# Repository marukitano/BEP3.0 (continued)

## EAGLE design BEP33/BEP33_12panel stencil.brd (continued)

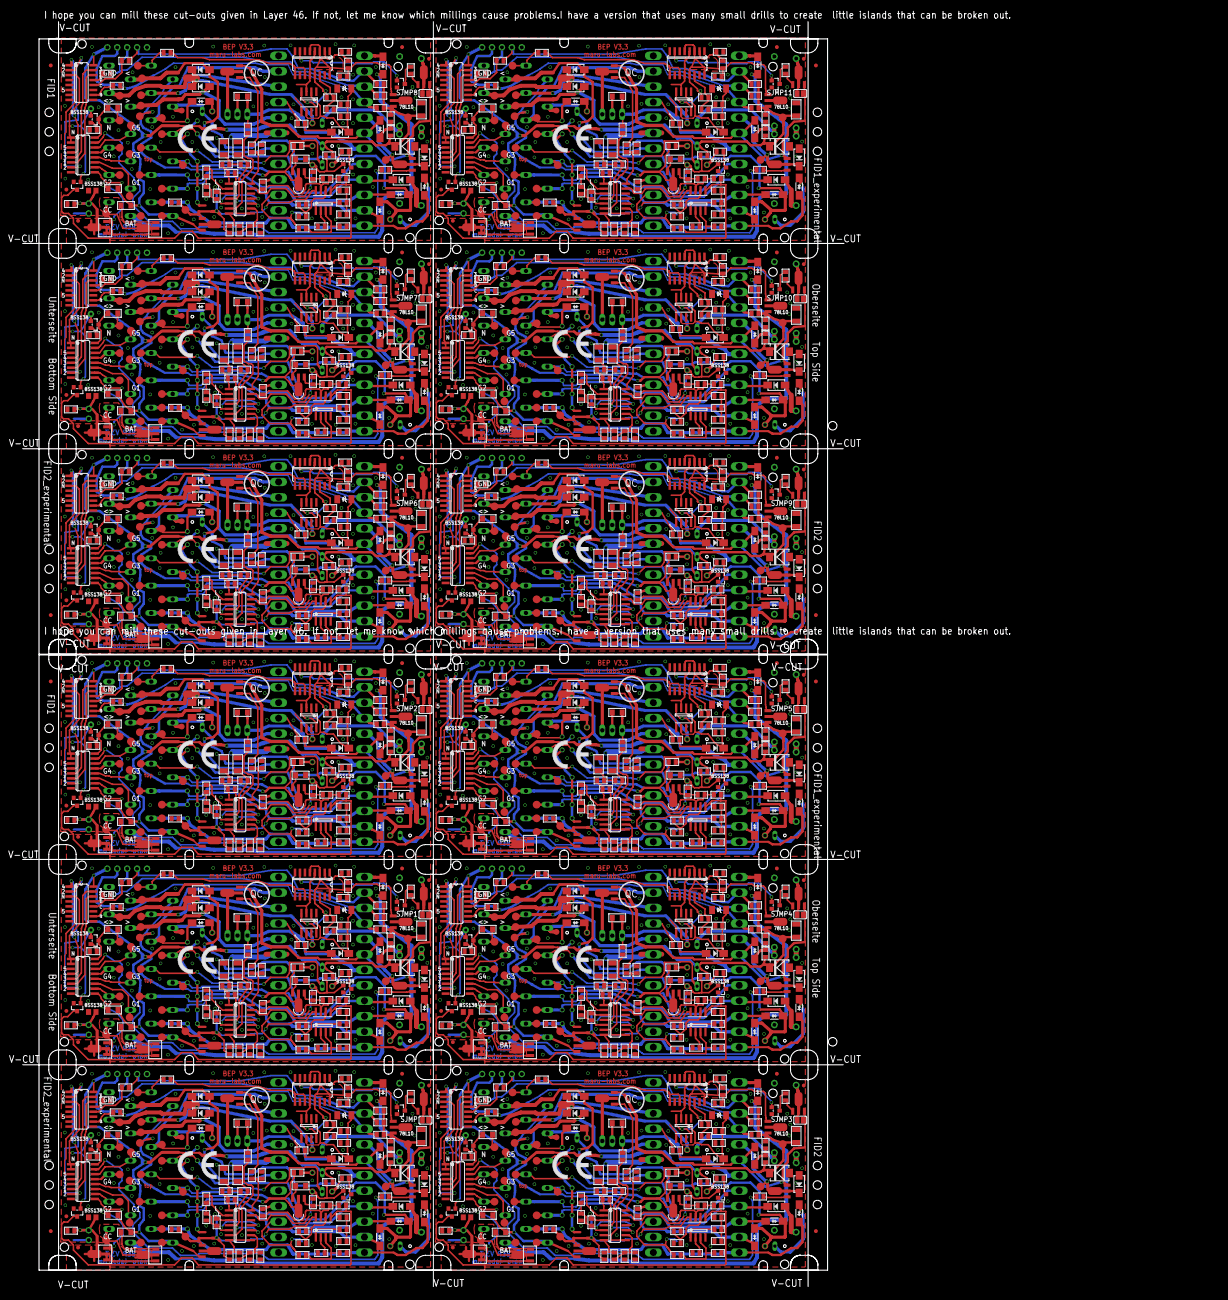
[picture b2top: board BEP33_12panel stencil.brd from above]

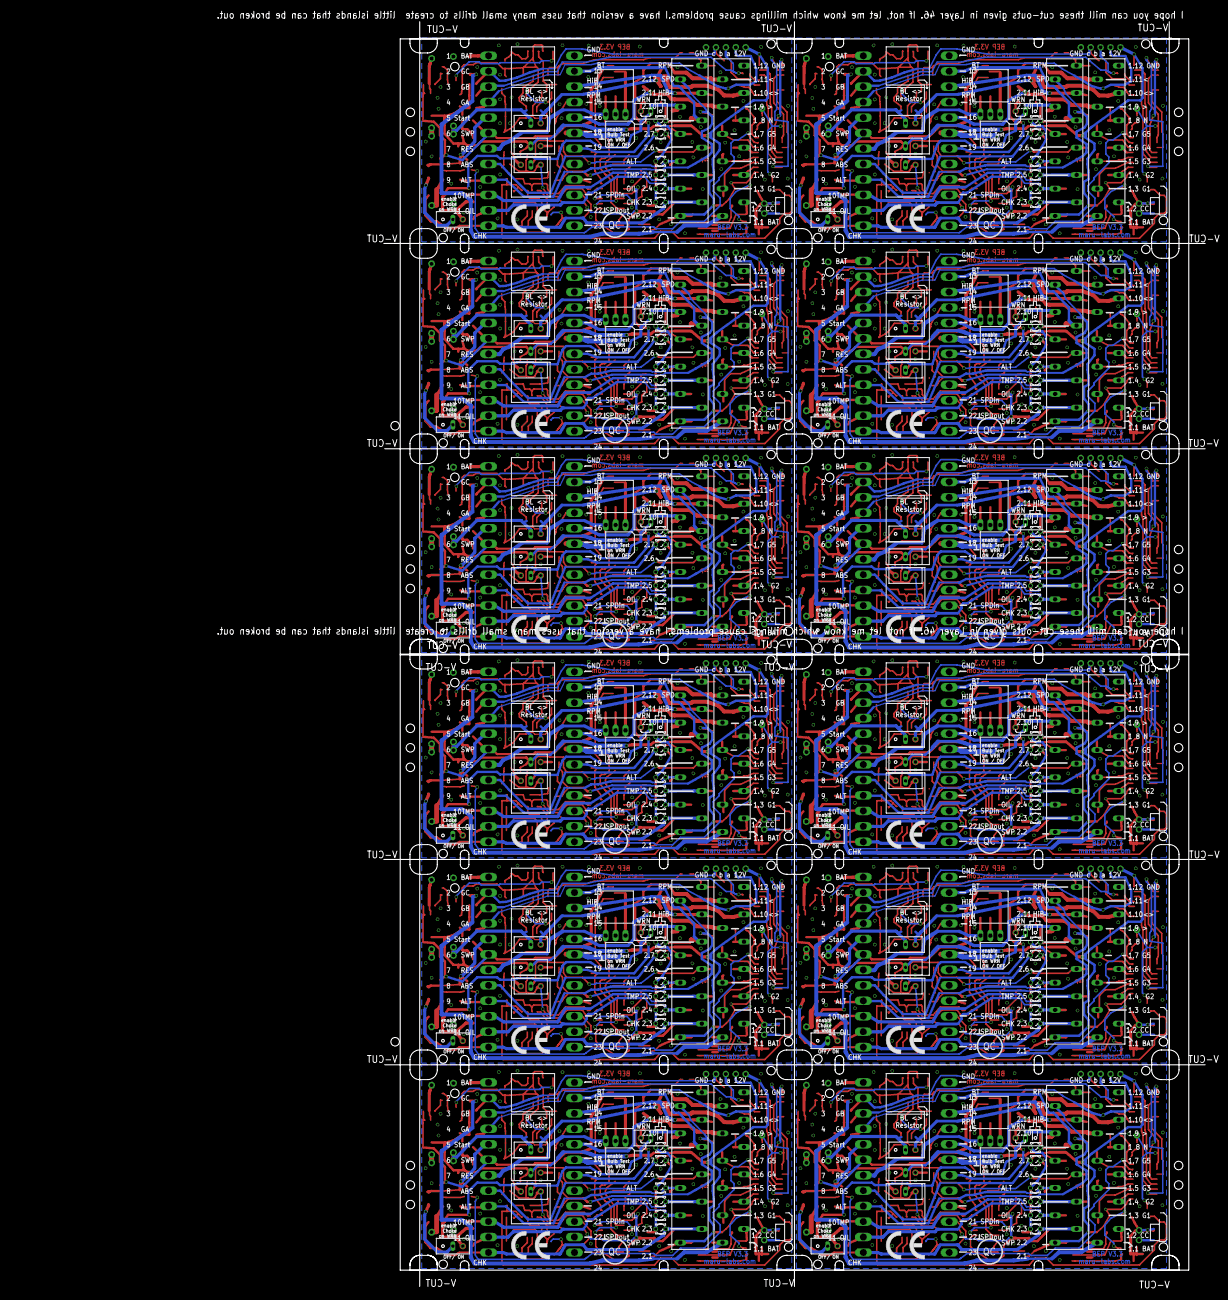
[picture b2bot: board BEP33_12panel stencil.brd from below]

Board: 2 copper layers, 210.4 x 324.0 mm, 1744 parts (264 on the bottom side), 1037 nets.

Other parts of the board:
U$1, U$2, U$3, U$4, U$5, U$6, U$7, U$8, U$9, U$10, U$11, U$12, U$37, U$38, U$39, U$40, U$41, U$42, U$43, U$44, U$45, U$46, U$47, U$48: CE_10.00

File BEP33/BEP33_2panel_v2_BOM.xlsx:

Qty | Value | Device | Package | Parts | Description | MF | MPN | OC_FARNELL | OC_NEWARK | TP | TP_SIGNAL_NAME | VALUE
2 | 100nF | CERAMIC-100NF-50V-10%-X7R(0805) | C0805 | C102, C110 | 302010165 |  | CC0805KRX7R9BB104 |  |  |  |  | 10K
2 | 100nF, | CERAMIC-100NF-50V-10%-X7R(0805) | C0805 | C103, C104 | 302010165 |  | CC0805KRX7R9BB104 |  |  |  |  | 100R
2 | 100nF. | CERAMIC-100NF-50V-10%-X7R(0805) | C0805 | C105, C106 | 302010165 |  | CC0805KRX7R9BB104 |  |  |  |  | 2.2K
1 | 2.2nF | CERAMIC-100NF-50V-10%-X7R(0805) | C0805 | C109 | 302010165 |  | CC0805KRX7R9BB104 |  |  |  |  | 220R
2 | 4.7u | CERAMIC-4.7UF-25V-10%-X5R(0805) | C0805 | C15, C101 | 302010146 |  | CC0805KKX5R8BB475 |  |  |  |  | 10K
2 | 100u | CERAMIC-100UF-6.3V-20%-X5R(1206) | C1206 | C107, C108 | 302010183 |  | GRM31CR60J107ME39L |  |  |  |  | 1K
1 | 10u | CERAMIC-100UF-6.3V-20%-X5R(1206) | C1206 | C2 | 302010183 |  | GRM31CR60J107ME39L |  |  |  |  | 4.7K
1 | Zen15 | SM6T | DO214AA | D101 | Z DIODE |  |  |  |  |  |  | 100nf
1 | SM6TDO214AA_BI | SM6TDO214AA_BI | DO214AA_BI | D104 | Z DIODE |  |  |  |  |  |  | 100nf
1 | 1N4007 | DIODE-GEN-PURPOSE-1KV-1A(DO-214AC) | DO-214AC | D112 | 304010013 |  | 1N4007 |  |  |  |  | 100nf
2 | 1N4007, | DIODE-GEN-PURPOSE-1KV-1A(DO-214AC) | DO-214AC | D102, D103 | 304010013 |  | 1N4007 |  |  |  |  | 100uf
2 | 1N4007. | DIODE-GEN-PURPOSE-1KV-1A(DO-214AC) | DO-214AC | D105, D106 | 304010013 |  | 1N4007 |  |  |  |  | 1K
2 | 1N5817 | DIODE-GEN-PURPOSE-1KV-1A(DO-214AC)DO-214AC/1206 | DO-214AC_SLIM | D107, D110 | 304010013 |  |  |  |  |  |  | 220R
2 | 1N5817. | DIODE-GEN-PURPOSE-1KV-1A(DO-214AC)DO-214AC/1206 | DO-214AC_SLIM | D108, D109 | 304010013 |  |  |  |  |  |  | 10K
2 | SS12 | DIODE-GEN-PURPOSE-1KV-1A(DO-214AC)DO-214AC/1206 | DO-214AC_SLIM | D1, D2 | 304010013 |  |  |  |  |  |  | 4.7K
1 | -1000 | SMD-RES-100R-5%-1/8W(0805) | R0805 | R142 | 301010319 |  | RC0805JR-07100RL |  |  |  |  | 1N4007
1 | -1002 | SMD-RES-10K-1%-1/8W(0805) | R0805 | R144 | 301010361 |  | RC0805FR-0710KL |  |  |  |  | 1N4007
1 | -101 | SMD-RES-100R-5%-1/8W(0805) | R0805 | R143 | 301010319 |  | RC0805JR-07100RL
3 | 100 | SMD-RES-2.2K-5%-1/8W(0805) | R0805 | R12, R13, R138 | 301010333 |  | RC0805JR-072K2L
1 | 100 | SMD-RES-220R-5%-1/8W(0805) | R0805 | R4 | 301010315 |  | RC0805JR-07220RL |  |  |  |  | 100nf
5 | 1002 | SMD-RES-10K-1%-1/8W(0805) | R0805 | R107, R108, R120, R124, R132 | 301010361 |  | RC0805FR-0710KL
2 | 1002 | SMD-RES-1K-5%-1/8W(0805) | R0805 | R113, R114 | 301010311 |  | RC0805JR-071KL
1 | 1002 | SMD-RES-4.7K-5%-1/8W(0805) | R0805 | R146 | 301010306 |  | RC0805JR-074K7L |  |  |  |  | 1K
3 | 102 | SMD-RES-1K-5%-1/8W(0805) | R0805 | R101, R112, R128 | 301010311 |  | RC0805JR-071KL |  |  |  |  | 2.2K
1 | 102 | SMD-RES-220R-5%-1/8W(0805) | R0805 | R115 | 301010315 |  | RC0805JR-07220RL |  |  |  |  | 10K
10 | 104 | SMD-RES-10K-1%-1/8W(0805) | R0805 | R1, R2, R3, R109, R110, R111, R125, R130, R135, R141 | 301010361 |  | RC0805FR-0710KL |  |  |  |  | 4.7K
1 | 104 | SMD-RES-4.7K-5%-1/8W(0805) | R0805 | R10 | 301010306 |  | RC0805JR-074K7L
2 | 1502 | SMD-RES-10K-1%-1/8W(0805) | R0805 | R121, R131 | 301010361 |  | RC0805FR-0710KL |  |  |  |  | 4.7uf
1 | 2201 | SMD-RES-1K-5%-1/8W(0805) | R0805 | R6 | 301010311 |  | RC0805JR-071KL
2 | 2201 | SMD-RES-2.2K-5%-1/8W(0805) | R0805 | R119, R133 | 301010333 |  | RC0805JR-072K2L
1 | 2702 | SMD-RES-10K-1%-1/8W(0805) | R0805 | R140 | 301010361 |  | RC0805FR-0710KL
4 | 2702 | SMD-RES-4.7K-5%-1/8W(0805) | R0805 | R117, R122, R123, R145 | 301010306 |  | RC0805JR-074K7L |  |  |  |  | 4.7K
4 | 4701 | SMD-RES-4.7K-5%-1/8W(0805) | R0805 | R8, R105, R116, R126 | 301010306 |  | RC0805JR-074K7L
5 | 13 | SMD-RES-13R-5%-1/4W(1206) | R1206 | R5, R9, R102, R106, R134 | 301010405 |  | RC1206JR-0713RL
1 | 555 | NE555D | SO08 | IC110 | TIMER
1 | LM2904 | LM358D | SO08 | IC101 | OP AMP also LM158; LM258; LM2904
1 | LM339 | LM339D | SO14 | IC108 | Low Power Low Offset Voltage Quad Comparators |  |  |  |  |  |  | BSS138W-7-F
1 | 4028 | 4028D | SO16 | IC105 | BCD to decimal DECODER
1 | 4538 | 4538D | SO16 | IC111 | Dual precision monostable MULTIVIBRATOR
1 | ULN2004 | ULN2004AD | SO16 | IC107 | DRIVER ARRAY
1 | Zen11 | CGRM4001-G | SOD-123_MINI-SMA | D4 | Molded plasitc,JEDEC SOD-123/Mini SMA
4 | J1 | SMD-MOSFET-N-CH-50V-200MA-BSS138W-7-F(SOT-23) | SOT-23 | Q1, Q3, Q106, Q107 | 305030000 |  | BSS138W-7-F
3 | BA | PNP-TRANSISTOR_SOT89 | SOT89 | Q2, Q104, Q105 | PNP TRANSISTOR
2 | BA. | PNP-TRANSISTOR_SOT89 | SOT89 | Q101, Q102 | PNP TRANSISTOR
1 | MY | NPN-TRANSISTOR_SOT89 | SOT89 | Q103 | NPN TRANSISTOR
1 | 78L06 | 78LXXSOT89_ROUND | SOT89_ROUND | IC102
1 | 78L10 | 78LXXSOT89_ROUND | SOT89_ROUND | IC104
1 | 317TO202H_NOHOLE | 317TO202H_NOHOLE | TO220H_NOHOLE | IC109 | Positive VOLTAGE REGULATOR
4 | 47 | R-EU_V235/17_1MM | V235/17_1MM | R127, R129, R136, R137 | RESISTOR, European symbol
